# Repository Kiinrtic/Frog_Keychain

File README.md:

# Frog_Keychain
A Frog shaped PCB keychain with 4 LEDs and a switch. The frog lights up when the switch is pressed. This project doesn't have any major features—it's just a fun, personalized creation.
This was my first pcb made  for the [solder event at hackclub](http://solder.hackclub.com/). I am very grateful that I got the chance to experience making circuits and wiring components. Thak you hackclub!

Items used:
- 4x 220 ohm resistors
- 4x LEDs
- 1 CR2032 battery with holder
- 1x 2 pin switch

Slack name: @Kiinrtic

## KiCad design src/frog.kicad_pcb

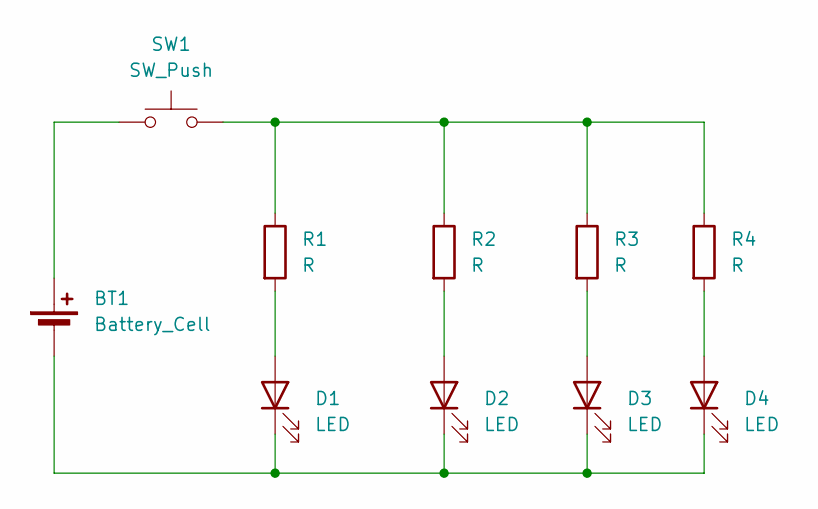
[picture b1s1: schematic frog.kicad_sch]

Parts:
BT1: Battery_Cell; BatteryHolder_Keystone_3034_1x20mm
D1, D2, D3, D4: LED; LED_D5.0mm
R1, R2, R3, R4: R; R_Axial_DIN0207_L6.3mm_D2.5mm_P7.62mm_Horizontal
SW1: SW_Push; SW_PUSH_6mm

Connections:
unnamed: BT1.1 (+), SW1.1
unnamed: BT1.2 (-), D1.1 (K), D2.1 (K), D3.1 (K), D4.1 (K)
unnamed: D1.2 (A), R1.2
unnamed: D2.2 (A), R2.2
unnamed: D3.2 (A), R3.2
unnamed: D4.2 (A), R4.2
unnamed: R1.1, R2.1, R3.1, R4.1, SW1.2

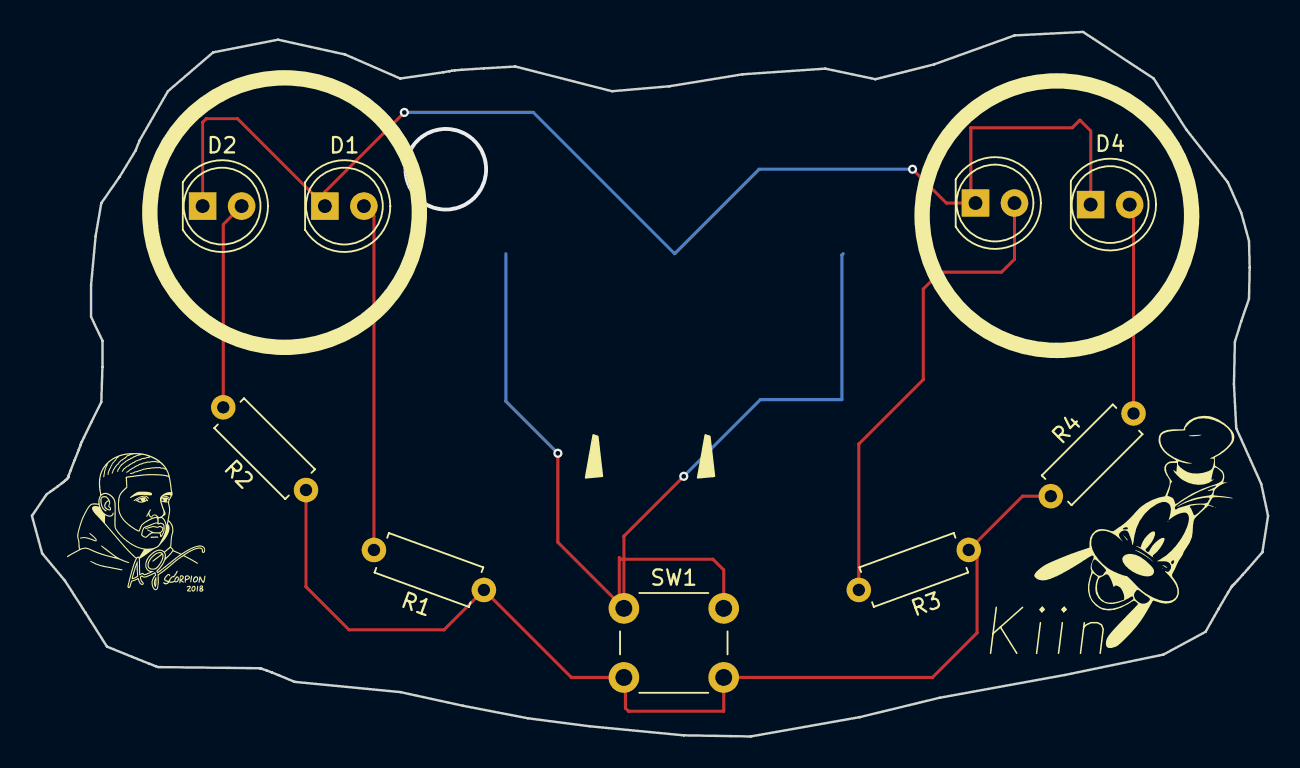
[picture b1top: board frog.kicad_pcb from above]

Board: 2 copper layers, 80.5 x 45.9 mm, 10 parts (1 on the bottom side), 7 nets.

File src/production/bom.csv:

Designator,Footprint,Quantity,Value,LCSC Part #
BT1,BatteryHolder_Keystone_3034_1x20mm,1,Battery_Cell,
"D1, D2, D3, D4",LED_D5.0mm,4,LED,
"R1, R2, R3, R4",R_Axial_DIN0207_L6.3mm_D2.5mm_P7.62mm_Horizontal,4,R,
SW1,SW_PUSH_6mm,1,SW_Push,

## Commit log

2025-05-29 This should be the final commit of this repo
2025-05-29 guess I was wrong
